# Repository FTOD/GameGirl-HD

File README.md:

GameGirl Hardware Development

[Schematics as PDF](schematics.pdf)
## To do better in the next version:
-   Impedance matching of D+/D- lines of USB
-   Use Lipo or Li-ion battery with embedded charger circuit
-   Embed the On-Off switch (some PMIC may have this kind of feature with tactile switches)
## License

Copyright (c) Caca 2021-1.
This source and all design files in the GameGirl project: https://github.com/FTOD/GameGirl-HD describe Open Hardware and is licensed under the CERN-OHL-P
v2
You may redistribute and modify this documentation and make products
using it under the terms of the CERN-OHL-P v2 (https:/cern.ch/cern-ohl).
This documentation is distributed WITHOUT ANY EXPRESS OR IMPLIED
WARRANTY, INCLUDING OF MERCHANTABILITY, SATISFACTORY QUALITY
AND FITNESS FOR A PARTICULAR PURPOSE. Please see the CERN-OHL-P v2
for applicable conditions

please refer to [cern_ohl_p_v2_howto.pdf](cern_ohl_p_v2_howto.pdf) for how to deal with this license.

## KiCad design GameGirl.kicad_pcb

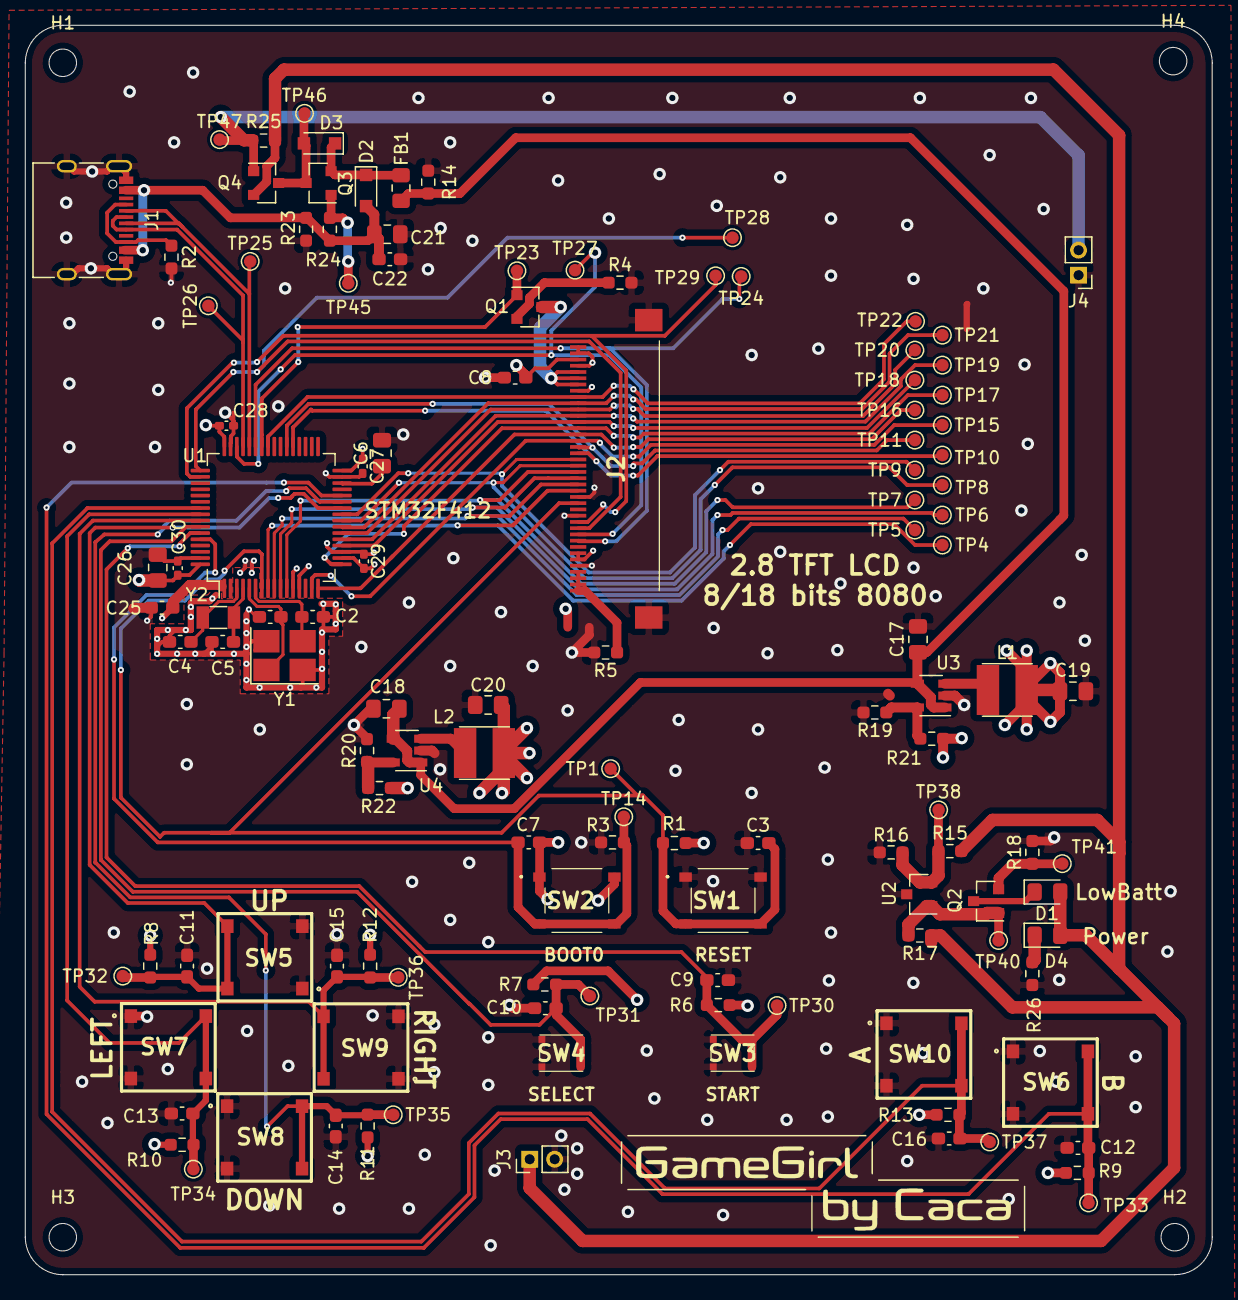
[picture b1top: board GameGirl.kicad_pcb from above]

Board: 4 copper layers, 95.0 x 100.0 mm, 128 parts (0 on the bottom side), 61 nets.

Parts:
C1, C2, C4, C5: 20pF; C_0603_1608Metric_Pad1.08x0.95mm_HandSolder
C3, C7: 100pF; C_0603_1608Metric_Pad1.08x0.95mm_HandSolder
C6, C17, C18: 4.7uF; C_0805_2012Metric_Pad1.18x1.45mm_HandSolder
C8: 1uF; C_0603_1608Metric_Pad1.08x0.95mm_HandSolder
C9, C10, C11, C12, C13, C14, C15, C16: 10nF; C_0603_1608Metric_Pad1.08x0.95mm_HandSolder
C19, C20, C21, C26: 10uF; C_0805_2012Metric_Pad1.18x1.45mm_HandSolder
C22: 0.1uF; C_0603_1608Metric_Pad1.08x0.95mm_HandSolder
C25: 100nF; C_0603_1608Metric_Pad1.08x0.95mm_HandSolder
C27, C28, C29, C30: 100nF; C_0402_1005Metric_Pad0.74x0.62mm_HandSolder
D1, D4: LED; LED_0805_2012Metric_Pad1.15x1.40mm_HandSolder
D2, D3: D_Shockley; D_SOD-323_HandSoldering
FB1: GZ2012D601TF; L_0805_2012Metric_Pad1.15x1.40mm_HandSolder
H1, H2, H3, H4: MountingHole; MountingHole_2.2mm_M2
J1: USB_C(U262-161N-4BVC11); USB_C_Receptacle_XKB_U262-16XN-4BVC11
J2: FH28-40S-0.5SH(07); FH2840S05SH07
J3, J4: PH_2; PinHeader_1x02_P2.00mm_Vertical
L1, L2: 2.2uH; L_TDK_VLCF4020x
Q1, Q2: AO3400(NMOS); SOT-23
Q3, Q4: AO3401; SOT-23
R1, R3, R6, R7, R8, R9, R10, R11, R12, R13, R14, R16, R23, R25: 10K; R_0603_1608Metric_Pad0.98x0.95mm_HandSolder
R2: 5.1K; R_0603_1608Metric_Pad0.98x0.95mm_HandSolder
R4: 10R; R_0603_1608Metric_Pad0.98x0.95mm_HandSolder
R5: 20K; R_0603_1608Metric_Pad0.98x0.95mm_HandSolder
R15: 3.3K; R_0603_1608Metric_Pad0.98x0.95mm_HandSolder
R17: 1K; R_0603_1608Metric_Pad0.98x0.95mm_HandSolder
R18, R26: 100R; R_0603_1608Metric_Pad0.98x0.95mm_HandSolder
R19, R20: 100K; R_0603_1608Metric_Pad0.98x0.95mm_HandSolder
R21: 430K; R_0603_1608Metric_Pad0.98x0.95mm_HandSolder
R22: 200K; R_0603_1608Metric_Pad0.98x0.95mm_HandSolder
R24: 4.7K; R_0603_1608Metric_Pad0.98x0.95mm_HandSolder
SW1, SW2: TS-1187; TS1187ABAB
SW3, SW4: SKSHAAE010
SW5, SW6, SW7, SW8, SW9, SW10: SKRRAAE010; SKRR
TP1, TP4, TP5, TP6, TP7, TP8, TP9, TP10, TP11, TP14, TP30, TP31, TP32, TP33, TP34, TP35, TP36, TP37: TestPoint_Small; TestPoint_Pad_D1.0mm
TP15, TP16, TP17, TP18, TP19, TP20, TP21, TP22, TP23, TP24, TP25, TP26, TP27, TP28, TP29: DB0; TestPoint_Pad_D1.0mm
TP38: VREF_LED; TestPoint_Pad_D1.0mm
TP40: VTRIG_LED; TestPoint_Pad_D1.0mm
TP41: VLED; TestPoint_Pad_D1.0mm
TP45: 5V TRIG; TestPoint_Pad_D1.0mm
TP46: VBAT OUT; TestPoint_Pad_D1.0mm
TP47: VBATT_TRIG; TestPoint_Pad_D1.0mm
U1: STM32F412RET6; LQFP-64_10x10mm_P0.5mm
U2: TL431; SOT-23
U3, U4: TLV62569DBV; SOT-23-5
Y1: X322525-25MHz 12pF; Crystal_SMD_3225-4Pin_3.2x2.5mm_HandSoldering
Y2: FC135-32.768kHz 12.5pF; Crystal_SMD_3215-2Pin_3.2x1.5mm

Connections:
+1V8: C7.1, C20.1, C25.1, C26.1, C27.1, C28.1, C29.1, C30.1, L2.2, R1.1, R22.2, SW2.1, SW2.2, U1.1, U1.13, U1.19, U1.32, U1.48, U1.64
+3V3: C8.1, C19.1, J2.6, J2.7, J2.33, J2.38, L1.2, R6.1, R7.1, R8.1, R9.1, R10.1, R11.1, R12.1, R13.1, R21.2
+5V: C21.1, C22.1, D2.2, J1.A4, J1.A9, J1.B4, J1.B9, R23.1, R24.1
+BATT: D1.2, D4.2, J3.1, Q4.2, R15.1, R17.1, R25.1
/B0: C11.1, R8.2, SW5.3, SW5.4, TP32.1, U1.26
/B1: C14.1, R11.2, SW8.3, SW8.4, TP35.1, U1.27
/B2: C12.1, R9.2, SW6.3, SW6.4, TP33.1, U1.28
/B3: C16.1, R13.2, SW10.3, SW10.4, TP37.1, U1.55
/B4: C13.1, R10.2, SW7.3, SW7.4, TP34.1, U1.56
/B5: C15.1, R12.2, SW9.3, SW9.4, TP36.1, U1.57
/B6: C10.1, R7.2, SW4.3, SW4.4, TP31.1, U1.58
/B7: C9.1, R6.2, SW3.3, SW3.4, TP30.1, U1.59
/BOOT0: C7.2, R3.1, SW2.3, SW2.4, TP14.1, U1.60
/D10: J2.25, TP15.1, U1.15
/D11: J2.26, TP16.1, U1.16
/D12: J2.27, TP17.1, U1.17
/D13: J2.28, TP18.1, U1.20
/D14: J2.29, TP19.1, U1.21
/D15: J2.30, TP20.1, U1.22
/D16: J2.31, TP21.1, U1.23
/D17: J2.32, TP22.1, U1.41
/DB0: J2.17, TP4.1, U1.8
/DB1: J2.18, TP5.1, U1.9
/DB2: J2.19, TP6.1, U1.10
/DB3: J2.20, TP7.1, U1.11
/DB4: J2.21, TP8.1, U1.24
/DB5: J2.22, TP9.1, U1.25
/DB6: J2.23, TP10.1, U1.37
/DB7: J2.24, TP11.1, U1.38
/DCX: J2.10, TP27.1, U1.46
/HSE_IN: C1.1, U1.5, Y1.1
/HSE_OUT: C2.1, U1.6, Y1.3
/K: J2.34, J2.35, J2.36, Q1.3
/LSE_IN: C4.1, U1.3, Y2.1
/LSE_OUT: C5.1, U1.4, Y2.2
/USB_DN: J1.A7, J1.B7, TP25.1, U1.44
/USB_DP: J1.A6, J1.B6, TP26.1, U1.45
/XL: J2.1, J2.2, J2.3, J2.4, R5.1
/XLED_CTRL: Q1.1, TP23.1, U1.42
/~CSX: J2.9, TP24.1, U1.43
/~NRST: C3.2, J2.15, R1.2, SW1.3, SW1.4, TP1.1, U1.7
/~RDX: J2.12, TP29.1, U1.50
/~WRX: J2.11, TP28.1, U1.49
GND: C1.2, C2.2, C3.1, C4.2, C5.2, C6.2, C8.2, C9.2, C10.2, C11.2, C12.2, C13.2, C14.2, C15.2, C16.2, C17.2, C18.2, C19.2, C20.2, C21.2, C22.2, C25.2, C26.2, C27.2, C28.2, C29.2, C30.2, J1.A1, J1.A12, J1.B1, J1.B12, J1.S1, J2.5, J2.13, J2.16, J2.37, J2.39, J2.40, J2.MP1, J2.MP2, J3.2, J4.1, R2.2, R3.2, R4.2, R5.2, R14.2, R16.2, R18.2, R19.2, R20.2, R23.2, R26.2, SW1.1, SW1.2, SW3.1, SW3.2, SW4.1, SW4.2, SW5.1, SW5.2, SW6.1, SW6.2, SW7.1, SW7.2, SW8.1, SW8.2, SW9.1, SW9.2, SW10.1, SW10.2, U1.12, U1.18, U1.31, U1.47, U1.63, U2.3, U3.2, U4.2, Y1.2, Y1.4
unnamed: C6.1, U1.30
unnamed: D1.1, Q2.3
unnamed: D2.1, D3.1, FB1.2, Q3.2
unnamed: D3.2, Q3.3, Q4.3, TP46.1
unnamed: D4.1, R26.1
unnamed: J1.A5, J1.B5, R2.1
unnamed: J4.2, Q4.1, R25.2, TP47.1
unnamed: L1.1, U3.3
unnamed: L2.1, U4.3
unnamed: Q1.2, R4.1
unnamed: Q2.1, R17.2, TP40.1, U2.1
unnamed: Q2.2, R18.1, TP41.1
unnamed: Q3.1, R24.2, TP45.1
unnamed: R15.2, R16.1, TP38.1, U2.2
unnamed: R19.1, R21.1, U3.5
unnamed: R20.1, R22.1, U4.5
VDC: C17.1, C18.1, FB1.1, R14.1, U3.1, U3.4, U4.1, U4.4

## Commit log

2022-01-07 first commit, almost all files are added, maybe eeds a bit of clean up
2022-01-07 add schematics pdf
2022-01-09 add product image
2022-01-09 merge
2022-01-09 add missing 3D models, new rendering
2022-01-13 add license
